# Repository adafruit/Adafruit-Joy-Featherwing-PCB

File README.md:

## Adafruit Joy FeatherWing PCB

<a href="http://www.adafruit.com/products/3632"><br/>
Click here to purchase one from the Adafruit shop</a>

PCB files for joy featherwing. Format is EagleCAD schematic and board layout

For more details, check out the product page at
* https://www.adafruit.com/products/3632

### Description

Make a game or robotic controller with this Joy-ful FeatherWing. This FeatherWing has a 2-axis joystick and 5 momentary buttons (4 large and 1 small) so you can turn your feather board into a tiny game controller. This wing communicates with your host microcontroller over I2C so it's easy to use and doesn't take up any of your precious analog or digital pins. There is also an optional interrupt pin that can alert your feather when a button has been pressed or released to free up processor time for other tasks.

This FeatherWing features Adafruit Seesaw technology - a custom programmed little helper microcontroller that takes the two analog inputs from the joystick, and 5 button inputs, and converts it into a pretty I2C interface. This I2C interface means you don't 'lose' any GPIO or analog inputs when using this 'Wing, and it works with any and all Feathers! You can easily stack this with any other FeatherWing because I2C is a shared bus. If you have an I2C address conflict, or you want to connect more than one of these to a Feather, there are two address-select jumpers so you have 4 options of I2C addresses.

There's an optional IRQ (interrupt) line that you can use if you'd like the Wing to let you know when a button has been pressed. Since its optional (and most Feathers are perfectly happy polling the Wing for data) we left a bunch of solder jumpers so you can select what pin has the IRQ on it. Or just leave it disconnected!

We have an Adafruit Seesaw library for Arduino, Python and CircuitPython so you can get started with the Joy FeatherWing in a jiffy.

Comes with one assembled and programmed Wing, and two pieces of 0.1" header. Some soldering is required to attach the headers to the FeatherWing.

### License

Adafruit invests time and resources providing this open source design, please support Adafruit and open-source hardware by purchasing products from [Adafruit](https://www.adafruit.com)!

Designed by Limor Fried/Ladyada for Adafruit Industries.

Creative Commons Attribution/Share-Alike, all text above must be included in any redistribution. See license.txt for additional details.

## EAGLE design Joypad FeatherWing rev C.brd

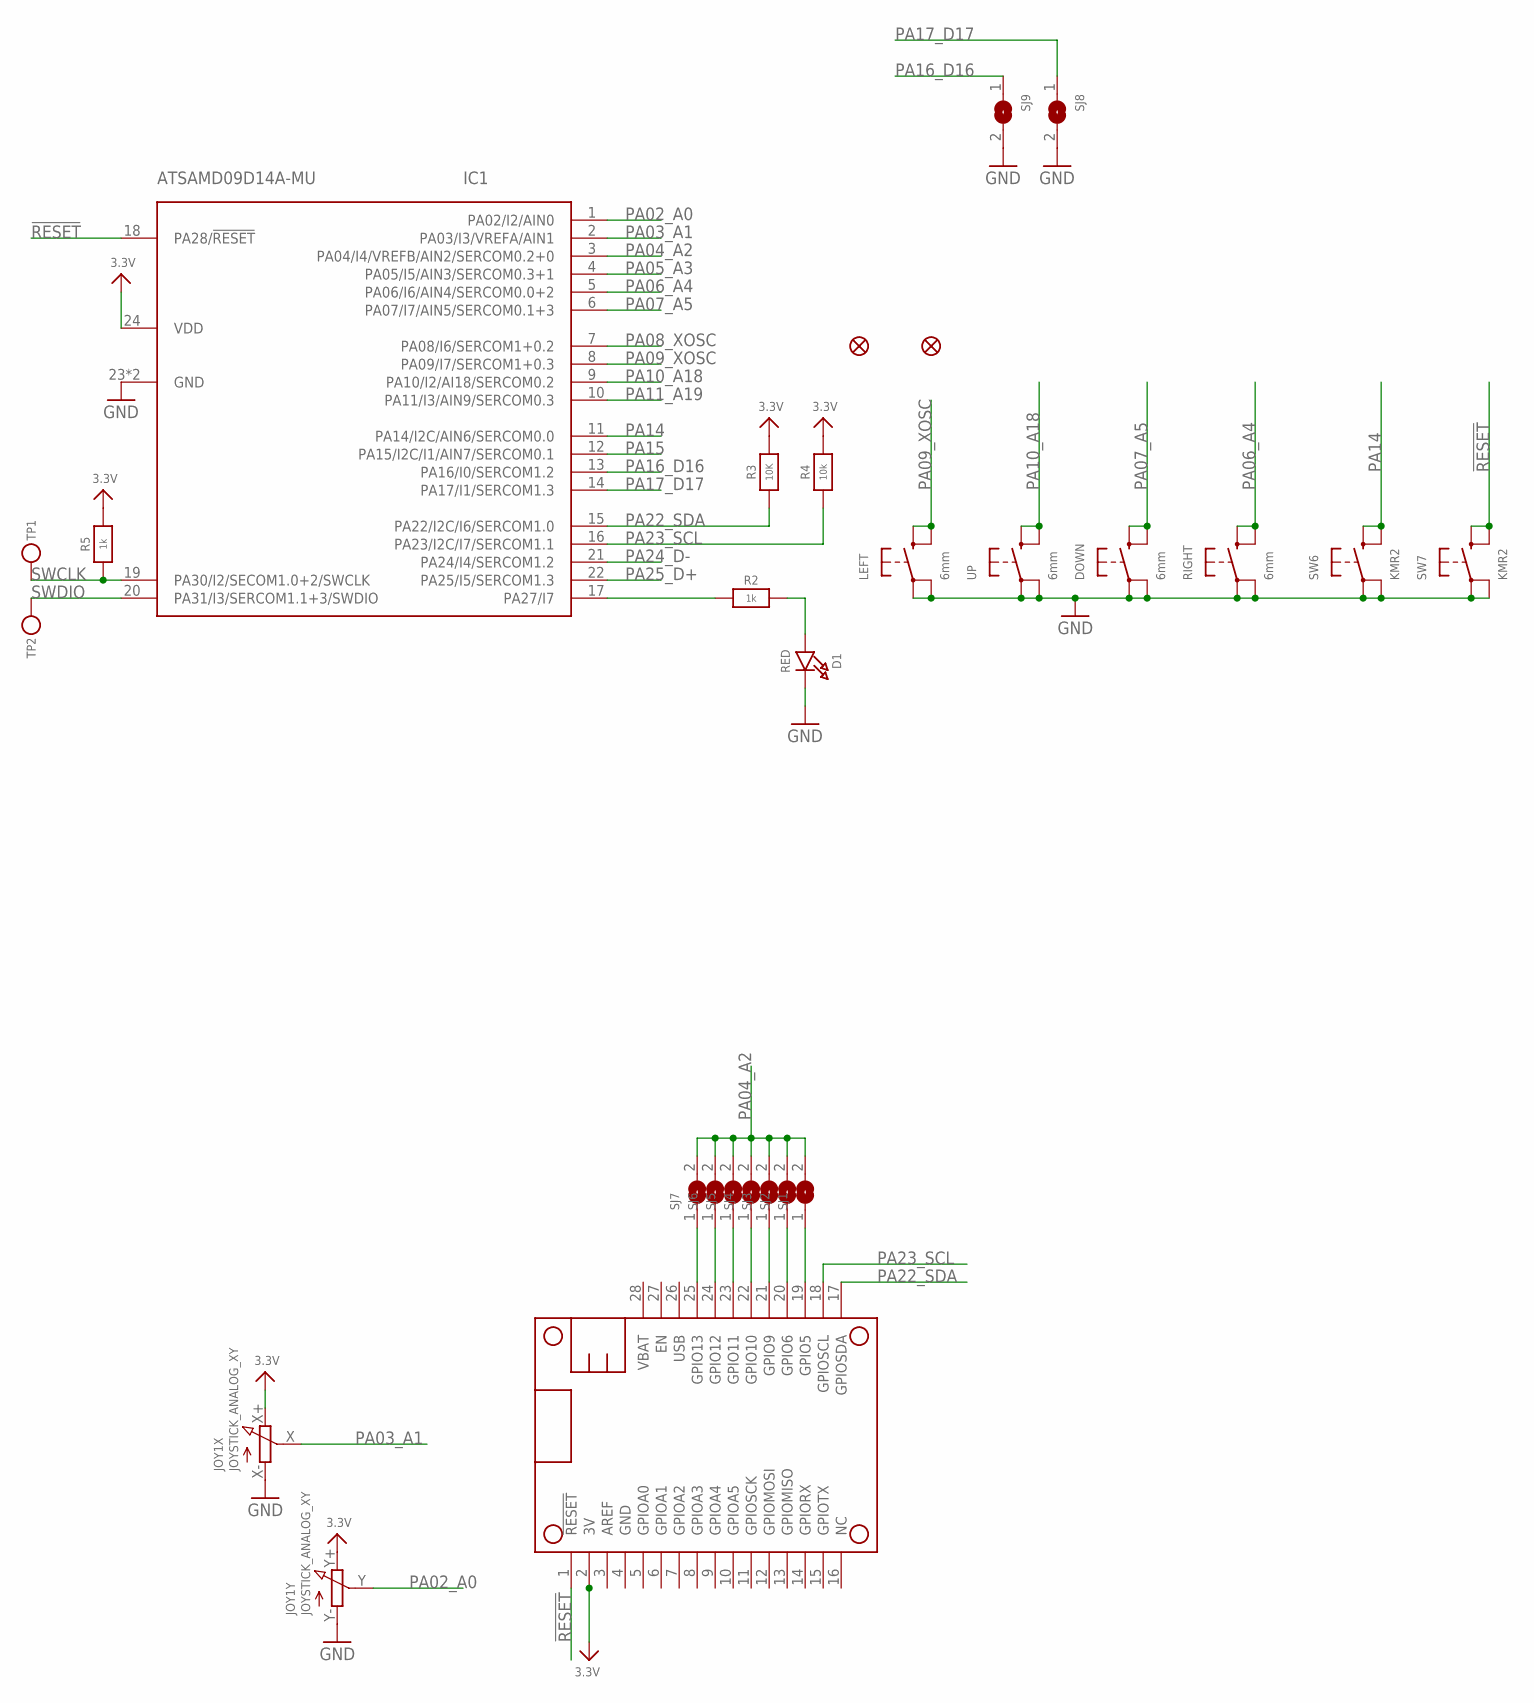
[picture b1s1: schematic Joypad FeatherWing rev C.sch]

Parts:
D1: RED; CHIPLED_0805_NOOUTLINE
DOWN: 6mm; EVQ-Q2_SMALLER
FID1, FID2: FIDUCIAL_1MM
IC1: ATSAMD09D14A-MU; QFN24_4MM
JOY1: JOYSTICK_ANALOG_XY; JOYSTICK_ANALOG_MINITHM
LEFT: 6mm; EVQ-Q2_SMALLER
MS1: FEATHERWING
R2, R5: 1k; 0603-NO
R3: 10K; 0603-NO
R4: 10k; 0603-NO
RIGHT: 6mm; EVQ-Q2_SMALLER
SJ1, SJ2, SJ3, SJ4, SJ5, SJ6, SJ7, SJ8, SJ9: SOLDERJUMPER; SOLDERJUMPER_ARROW_NOPASTE
SW6, SW7: KMR2; BTN_KMR2_4.6X2.8
TP1, TP2: TESTPOINTROUND2MM; TESTPOINT_ROUND_2MM
UP: 6mm; EVQ-Q2_SMALLER

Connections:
3.3V: IC1.24 (VDD), JOY1.X+ (E), JOY1.Y+ (E), MS1.2 (3V), R3.2, R4.2, R5.2
!RESET: IC1.18 (PA28/!RESET), MS1.1 (!RESET), SW7.B (S), SW7.B' (S1)
GND: D1.C, DOWN.A, DOWN.A' (P1), IC1.23 (GND), IC1.THERM (GND), JOY1.X- (A), JOY1.Y- (A), LEFT.A, LEFT.A' (P1), MS1.4 (GND), RIGHT.A, RIGHT.A' (P1), SJ8.2, SJ9.2, SW6.A, SW6.A' (P1), SW7.A, SW7.A' (P1), UP.A, UP.A' (P1)
unnamed: MS1.19 (GPIO5), SJ1.1
unnamed: MS1.20 (GPIO6), SJ2.1
unnamed: MS1.21 (GPIO9), SJ3.1
unnamed: MS1.22 (GPIO10), SJ4.1
unnamed: IC1.17 (PA27/I7), R2.1
unnamed: MS1.23 (GPIO11), SJ5.1
unnamed: MS1.24 (GPIO12), SJ6.1
unnamed: MS1.25 (GPIO13), SJ7.1
unnamed: D1.A, R2.2
PA02_A0: IC1.1 (PA02/I2/AIN0), JOY1.Y (S)
PA03_A1: IC1.2 (PA03/I3/VREFA/AIN1), JOY1.X (S)
PA04_A2: IC1.3 (PA04/I4/VREFB/AIN2/SERCOM0.2+0), SJ1.2, SJ2.2, SJ3.2, SJ4.2, SJ5.2, SJ6.2, SJ7.2
PA05_A3: IC1.4 (PA05/I5/AIN3/SERCOM0.3+1)
PA06_A4: IC1.5 (PA06/I6/AIN4/SERCOM0.0+2), RIGHT.B (S), RIGHT.B' (S1)
PA07_A5: DOWN.B (S), DOWN.B' (S1), IC1.6 (PA07/I7/AIN5/SERCOM0.1+3)
PA08_XOSC: IC1.7 (PA08/I6/SERCOM1+0.2)
PA09_XOSC: IC1.8 (PA09/I7/SERCOM1+0.3), LEFT.B (S), LEFT.B' (S1)
PA10_A18: IC1.9 (PA10/I2/AI18/SERCOM0.2), UP.B (S), UP.B' (S1)
PA11_A19: IC1.10 (PA11/I3/AIN9/SERCOM0.3)
PA14: IC1.11 (PA14/I2C/AIN6/SERCOM0.0), SW6.B (S), SW6.B' (S1)
PA15: IC1.12 (PA15/I2C/I1/AIN7/SERCOM0.1)
PA16_D16: IC1.13 (PA16/I0/SERCOM1.2), SJ9.1
PA17_D17: IC1.14 (PA17/I1/SERCOM1.3), SJ8.1
PA22_SDA: IC1.15 (PA22/I2C/I6/SERCOM1.0), MS1.17 (GPIOSDA), R3.1
PA23_SCL: IC1.16 (PA23/I2C/I7/SERCOM1.1), MS1.18 (GPIOSCL), R4.1
PA24_D-: IC1.21 (PA24/I4/SERCOM1.2)
PA25_D+: IC1.22 (PA25/I5/SERCOM1.3)
SWCLK: IC1.19 (PA30/I2/SECOM1.0+2/SWCLK), R5.1, TP1.P$1
SWDIO: IC1.20 (PA31/I3/SERCOM1.1+3/SWDIO), TP2.P$1

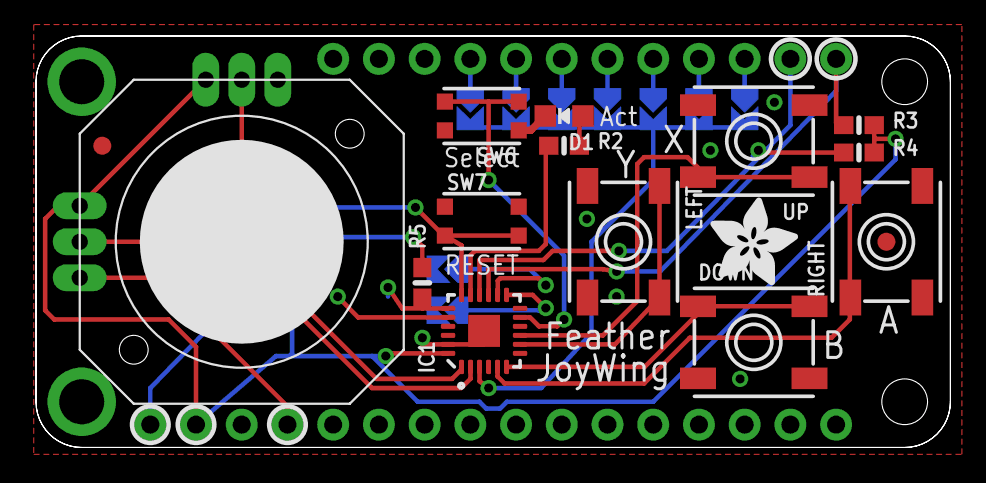
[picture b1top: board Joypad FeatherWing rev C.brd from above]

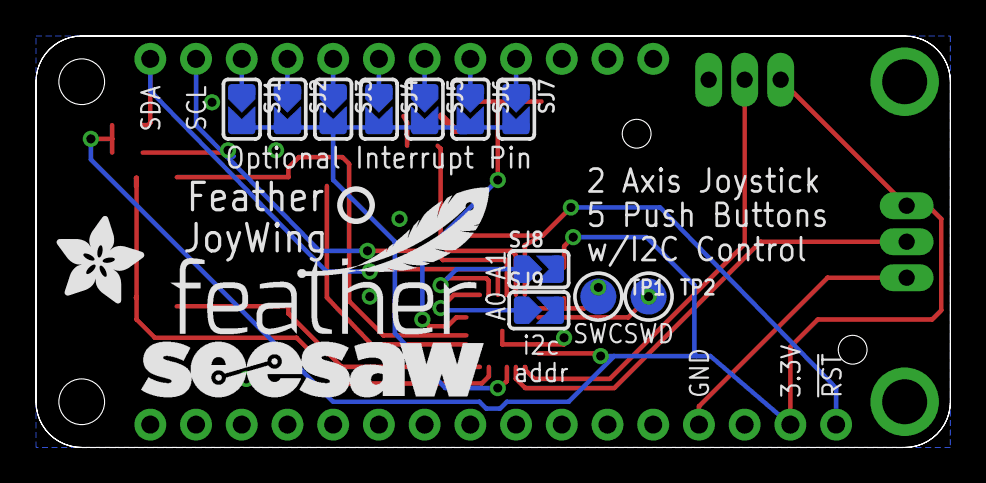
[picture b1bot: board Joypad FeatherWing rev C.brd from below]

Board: 2 copper layers, 50.8 x 22.9 mm, 32 parts (15 on the bottom side), 26 nets.

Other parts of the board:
U$7: PCBFEAT-REV-040
U$9, U$11: ADAFRUIT_5MM
U$10: FEATHERLOGO_MED
U$12: SEESAW_LOGO

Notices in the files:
parts and their libraries:
microbuilder: This work is placed in the public domain, and may be freely used for commercial and non-commercial work with the following conditions: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
